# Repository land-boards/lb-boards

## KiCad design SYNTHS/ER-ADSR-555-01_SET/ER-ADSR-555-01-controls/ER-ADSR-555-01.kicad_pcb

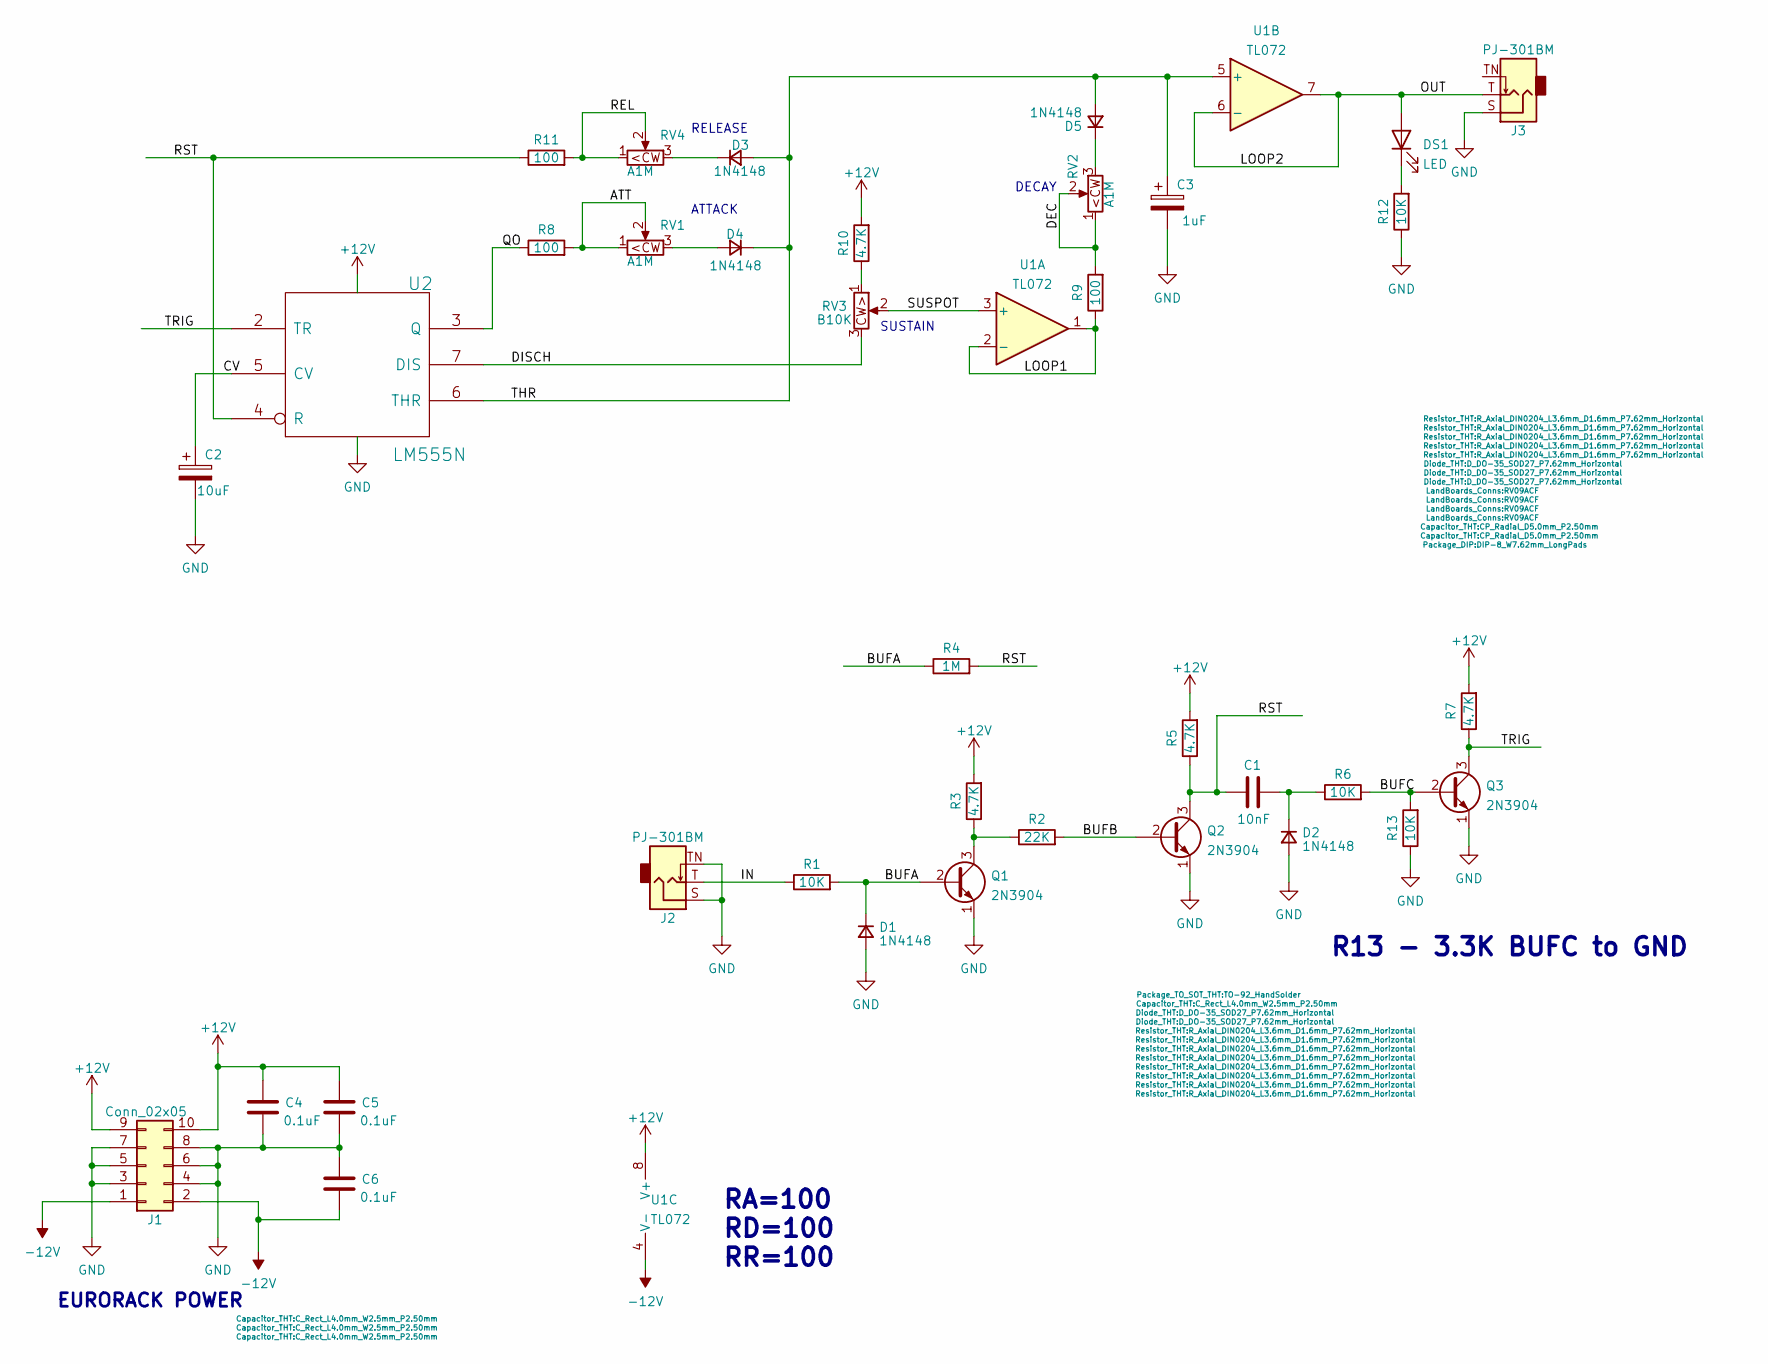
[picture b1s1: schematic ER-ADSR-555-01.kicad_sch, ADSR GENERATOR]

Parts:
C1: 10nF; C_Rect_L4.0mm_W2.5mm_P2.50mm
C2: 10uF; CP_Radial_D5.0mm_P2.50mm
C3: 1uF; CP_Radial_D5.0mm_P2.50mm
C4, C5, C6: 0.1uF; C_Rect_L4.0mm_W2.5mm_P2.50mm
D1, D2, D3, D4, D5: 1N4148; D_DO-35_SOD27_P7.62mm_Horizontal
DS1: LED; LED_D5.0mm
J1: Conn_02x05; IDC-Header_2x05_P2.54mm_Vertical
J2, J3: PJ-301BM; Jack_3.5mm_QingPu_WQP-PJ301BM_Vertical
Q1, Q2, Q3: 2N3904; TO-92_HandSolder
R1, R6, R12, R13: 10K; R_Axial_DIN0204_L3.6mm_D1.6mm_P7.62mm_Horizontal
R2: 22K; R_Axial_DIN0204_L3.6mm_D1.6mm_P7.62mm_Horizontal
R3, R5, R7, R10: 4.7K; R_Axial_DIN0204_L3.6mm_D1.6mm_P7.62mm_Horizontal
R4: 1M; R_Axial_DIN0204_L3.6mm_D1.6mm_P7.62mm_Horizontal
R8, R9, R11: 100; R_Axial_DIN0204_L3.6mm_D1.6mm_P7.62mm_Horizontal
RV1, RV2, RV4: A1M; RV09ACF
RV3: B10K; RV09ACF
U1: TL072; DIP-8_W7.62mm
U2: LM555N; DIP-8_W7.62mm_LongPads

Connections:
+12V: C4.2, C5.2, J1.9, J1.10, R3.2, R5.2, R7.2, R10.2, U1.8 (V+), U2.8 (VCC)
-12V: C6.1, J1.1, J1.2, U1.4 (V-)
/ATT: R8.2, RV1.1, RV1.2
/BUFA: D1.1 (K), Q1.2 (B), R1.2, R4.1
/BUFB: Q2.2 (B), R2.2
/BUFC: Q3.2 (B), R6.2, R13.2
/CV: C2.1, U2.5 (CV)
/DEC: R9.2, RV2.1, RV2.2
/DISCH: RV3.3, U2.7 (DIS)
/IN: J2.T, R1.1
/LOOP1: R9.1, U1.1, U1.2 (-)
/LOOP2: DS1.2 (A), J3.T, U1.6 (-), U1.7
/QO: R8.1, U2.3 (Q)
/REL: R11.2, RV4.1, RV4.2
/RST: C1.1, Q2.3 (C), R4.2, R5.1, R11.1, U2.4 (R)
/SUSPOT: RV3.2, U1.3 (+)
/THR: C3.1, D3.2 (A), D4.1 (K), D5.2 (A), U1.5 (+), U2.6 (THR)
/TRIG: Q3.3 (C), R7.1, U2.2 (TR)
GND: C2.2, C3.2, C4.1, C5.1, C6.2, D1.2 (A), D2.2 (A), J1.3, J1.4, J1.5, J1.6, J1.7, J1.8, J2.S, J2.TN, J3.S, Q1.1 (E), Q2.1 (E), Q3.1 (E), R12.1, R13.1, U2.1 (GND)
unnamed: C1.2, D2.1 (K), R6.1
unnamed: D3.1 (K), RV4.3
unnamed: D4.2 (A), RV1.3
unnamed: D5.1 (K), RV2.3
unnamed: DS1.1 (K), R12.2
unnamed: Q1.3 (C), R2.1, R3.1
unnamed: R10.1, RV3.1

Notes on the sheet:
DECAY
EURORACK POWER
RA=100 RD=100 RR=100
R13 - 3.3K BUFC to GND
ATTACK
RELEASE
SUSTAIN

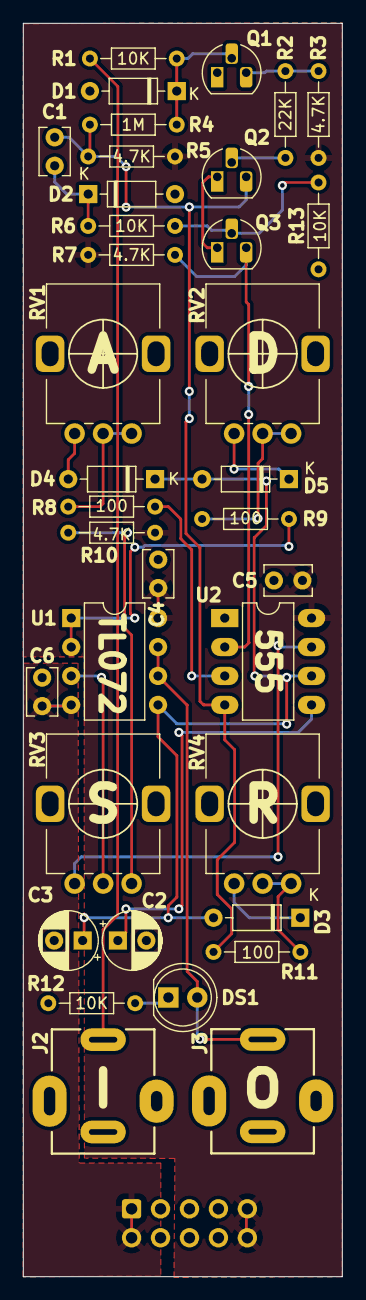
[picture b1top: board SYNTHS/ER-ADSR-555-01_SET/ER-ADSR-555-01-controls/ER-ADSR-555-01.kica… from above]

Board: 2 copper layers, 28.0 x 110.0 mm, 37 parts (1 on the bottom side), 26 nets.

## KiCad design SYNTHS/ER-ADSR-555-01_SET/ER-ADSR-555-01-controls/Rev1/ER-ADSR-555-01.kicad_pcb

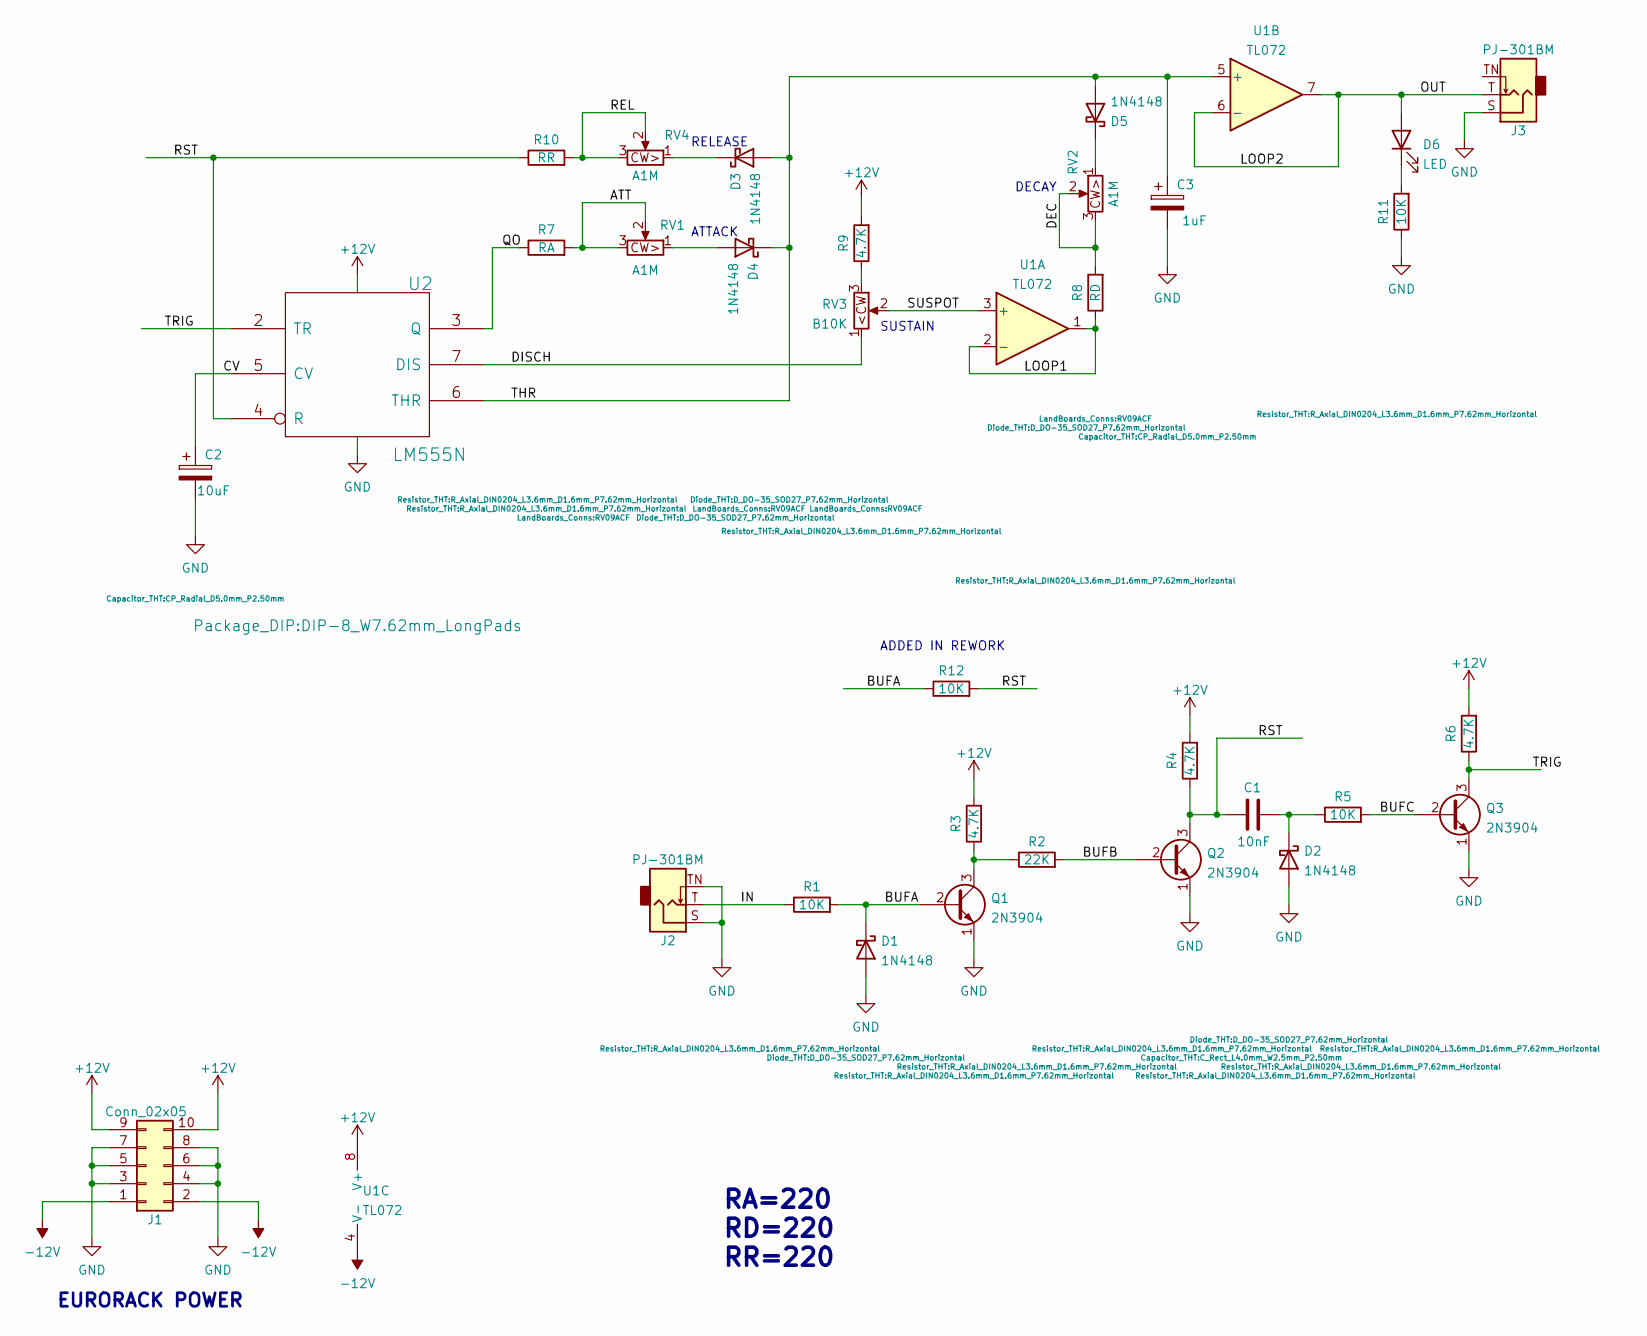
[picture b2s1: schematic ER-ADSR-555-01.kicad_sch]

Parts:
C1: 10nF; C_Rect_L4.0mm_W2.5mm_P2.50mm
C2: 10uF; CP_Radial_D5.0mm_P2.50mm
C3: 1uF; CP_Radial_D5.0mm_P2.50mm
D1, D2, D3, D4, D5: 1N4148; D_DO-35_SOD27_P7.62mm_Horizontal
D6: LED; LED_D5.0mm
J1: Conn_02x05; IDC-Header_2x05_P2.54mm_Vertical
J2, J3: PJ-301BM; Jack_3.5mm_QingPu_WQP-PJ301BM_Vertical
Q1, Q2, Q3: 2N3904; TO-92_Inline
R1, R5, R11, R12: 10K; R_Axial_DIN0204_L3.6mm_D1.6mm_P7.62mm_Horizontal
R2: 22K; R_Axial_DIN0204_L3.6mm_D1.6mm_P7.62mm_Horizontal
R3, R4, R6, R9: 4.7K; R_Axial_DIN0204_L3.6mm_D1.6mm_P7.62mm_Horizontal
R7: RA; R_Axial_DIN0204_L3.6mm_D1.6mm_P7.62mm_Horizontal
R8: RD; R_Axial_DIN0204_L3.6mm_D1.6mm_P7.62mm_Horizontal
R10: RR; R_Axial_DIN0204_L3.6mm_D1.6mm_P7.62mm_Horizontal
RV1, RV2, RV4: A1M; RV09ACF
RV3: B10K; RV09ACF
U1: TL072; DIP-8_W7.62mm
U2: LM555N; DIP-8_W7.62mm_LongPads

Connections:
+12V: J1.9, J1.10, R3.2, R4.2, R6.2, R9.2, U1.8 (V+), U2.8 (VCC)
-12V: J1.1, J1.2, U1.4 (V-)
/ATT: R7.2, RV1.2, RV1.3
/BUFA: D1.1 (K), Q1.2 (B), R1.2, R12.1
/BUFB: Q2.2 (B), R2.2
/BUFC: Q3.2 (B), R5.2
/CV: C2.1, U2.5 (CV)
/DEC: R8.2, RV2.2, RV2.3
/DISCH: RV3.1, U2.7 (DIS)
/IN: J2.T, R1.1
/LOOP1: R8.1, U1.1, U1.2 (-)
/LOOP2: D6.2 (A), J3.T, U1.6 (-), U1.7
/QO: R7.1, U2.3 (Q)
/REL: R10.2, RV4.2, RV4.3
/RST: C1.1, Q2.3 (C), R4.1, R10.1, R12.2, U2.4 (R)
/SUSPOT: RV3.2, U1.3 (+)
/THR: C3.1, D3.2 (A), D4.1 (K), D5.2 (A), U1.5 (+), U2.6 (THR)
/TRIG: Q3.3 (C), R6.1, U2.2 (TR)
GND: C2.2, C3.2, D1.2 (A), D2.2 (A), J1.3, J1.4, J1.5, J1.6, J1.7, J1.8, J2.S, J2.TN, J3.S, Q1.1 (E), Q2.1 (E), Q3.1 (E), R11.1, U2.1 (GND)
unnamed: C1.2, D2.1 (K), R5.1
unnamed: D3.1 (K), RV4.1
unnamed: D4.2 (A), RV1.1
unnamed: D5.1 (K), RV2.1
unnamed: D6.1 (K), R11.2
unnamed: Q1.3 (C), R2.1, R3.1
unnamed: R9.1, RV3.3

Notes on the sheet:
DECAY
EURORACK POWER
RA=220 RD=220 RR=220
ATTACK
RELEASE
SUSTAIN
ADDED IN REWORK

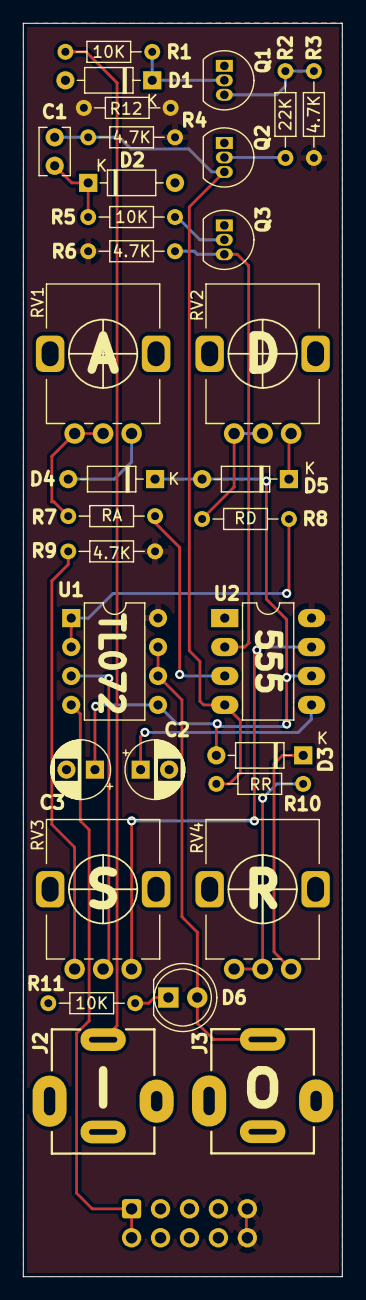
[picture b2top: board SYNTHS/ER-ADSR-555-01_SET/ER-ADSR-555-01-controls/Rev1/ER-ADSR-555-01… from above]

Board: 2 copper layers, 28.0 x 110.0 mm, 33 parts (1 on the bottom side), 26 nets.

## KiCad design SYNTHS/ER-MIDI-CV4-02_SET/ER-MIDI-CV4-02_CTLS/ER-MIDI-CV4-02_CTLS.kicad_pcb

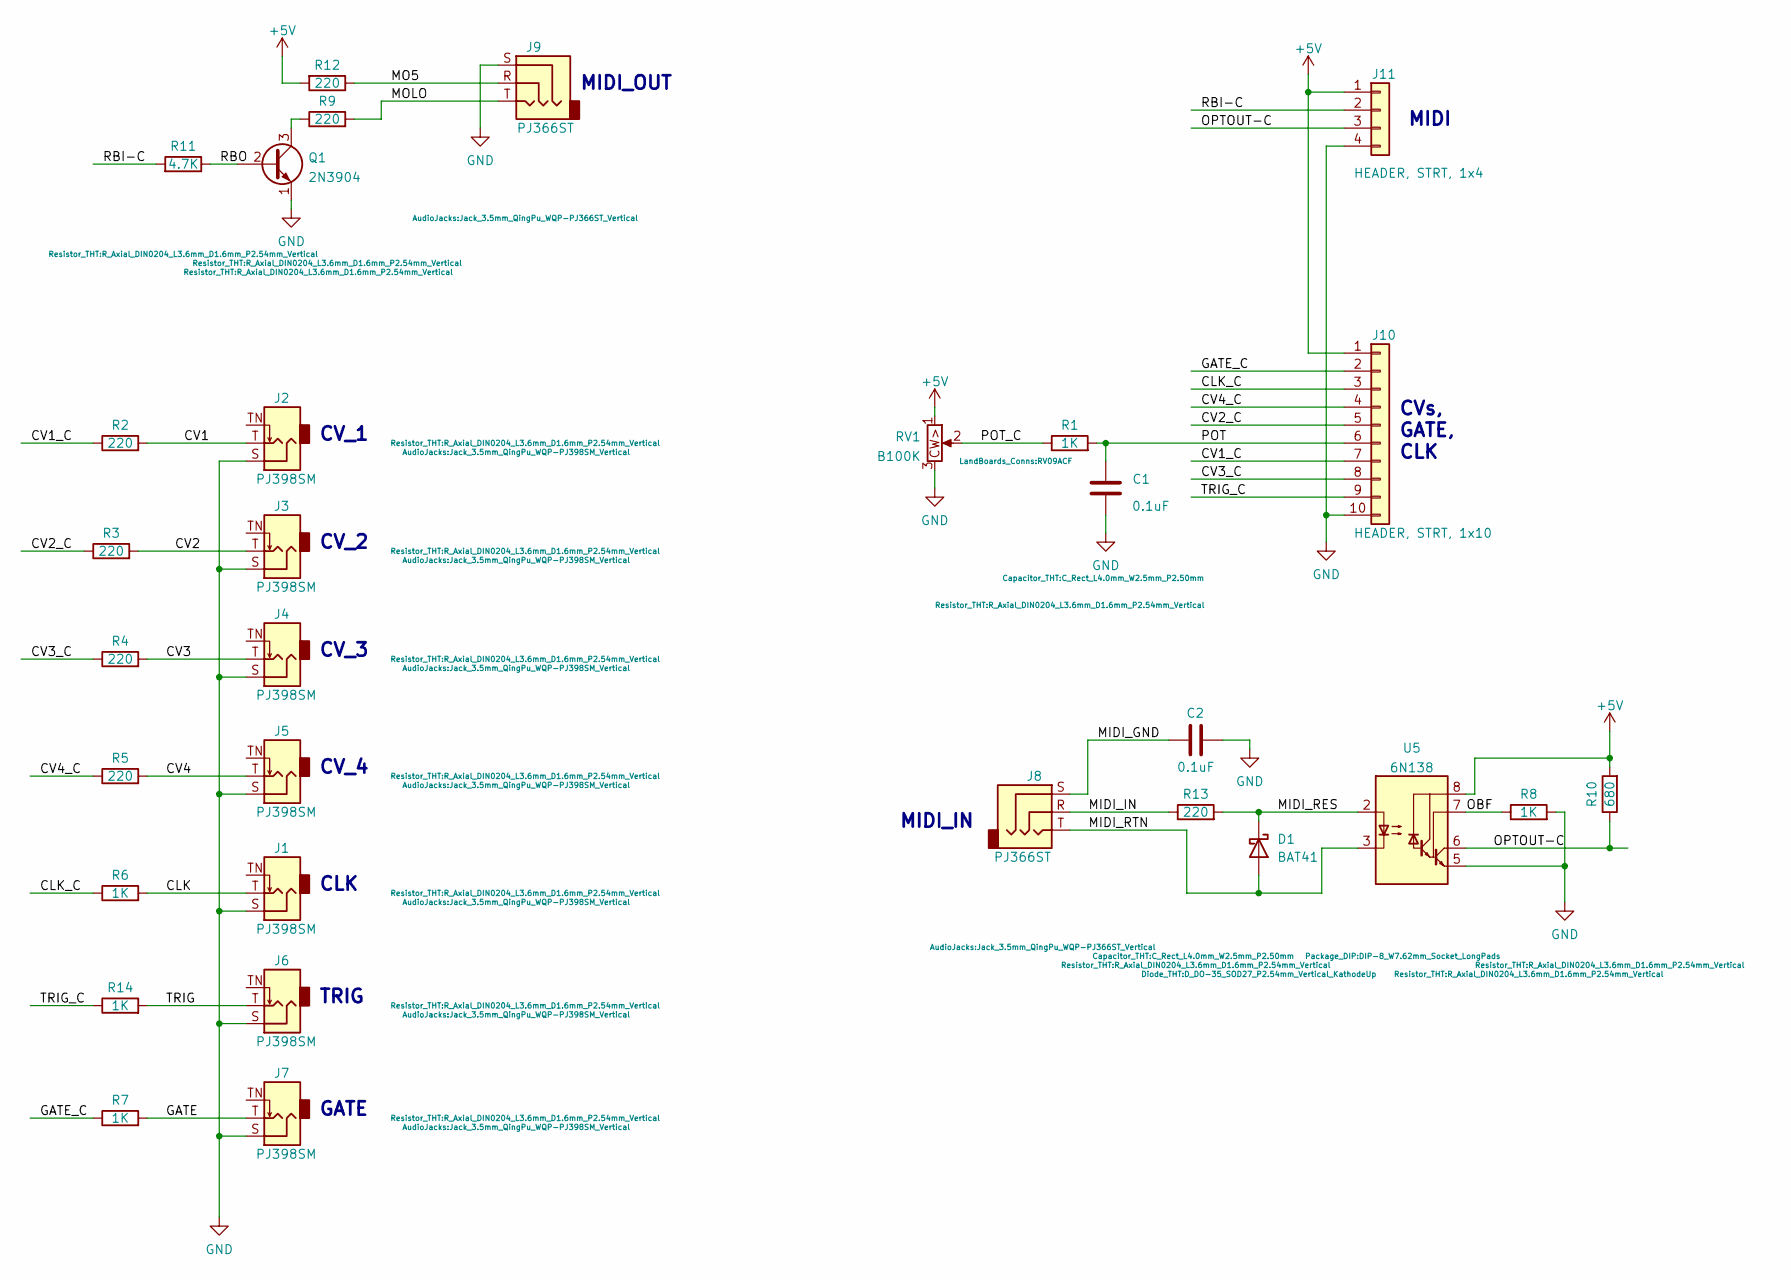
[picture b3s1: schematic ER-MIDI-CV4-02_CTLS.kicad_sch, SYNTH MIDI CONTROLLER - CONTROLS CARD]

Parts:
C1, C2: 0.1uF; C_Rect_L4.0mm_W2.5mm_P2.50mm
D1: BAT41; D_DO-35_SOD27_P2.54mm_Vertical_KathodeUp
J1, J2, J3, J4, J5, J6, J7: PJ398SM; Jack_3.5mm_QingPu_WQP-PJ398SM_Vertical
J8, J9: PJ366ST; Jack_3.5mm_QingPu_WQP-PJ366ST_Vertical
J10: HEADER, STRT, 1x10; PinHeader_1x10_P2.54mm_Vertical
J11: HEADER, STRT, 1x4; PinHeader_1x04_P2.54mm_Vertical
Q1: 2N3904; TO-92_Inline
R1, R6, R7, R8, R14: 1K; R_Axial_DIN0204_L3.6mm_D1.6mm_P2.54mm_Vertical
R2, R3, R4, R5, R9, R12, R13: 220; R_Axial_DIN0204_L3.6mm_D1.6mm_P2.54mm_Vertical
R10: 680; R_Axial_DIN0204_L3.6mm_D1.6mm_P2.54mm_Vertical
R11: 4.7K; R_Axial_DIN0204_L3.6mm_D1.6mm_P2.54mm_Vertical
RV1: B100K; RV09ACF
U5: 6N138; DIP-8_W7.62mm_Socket_LongPads

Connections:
+5V: J10.1, J11.1, R10.2, R12.2, RV1.1, U5.8 (VCC)
/CLK: J1.T, R6.2
/CLK_C: J10.3, R6.1
/CV1: J2.T, R2.2
/CV1_C: J10.7, R2.1
/CV2: J3.T, R3.2
/CV2_C: J10.5, R3.1
/CV3: J4.T, R4.2
/CV3_C: J10.8, R4.1
/CV4: J5.T, R5.2
/CV4_C: J10.4, R5.1
/GATE: J7.T, R7.2
/GATE_C: J10.2, R7.1
/MIDI_GND: C2.1, J8.S
/MIDI_IN: J8.R, R13.1
/MIDI_RES: D1.1 (K), R13.2, U5.2 (C1)
/MIDI_RTN: D1.2 (A), J8.T, U5.3 (C2)
/MO5: J9.R, R12.1
/MOLO: J9.T, R9.2
/OBF: R8.1, U5.7 (VO1)
/OPTOUT-C: J11.3, R10.1, U5.6 (VO2)
/POT: C1.2, J10.6, R1.2
/POT_C: R1.1, RV1.2
/RBI-C: J11.2, R11.2
/RBO: Q1.2 (B), R11.1
/TRIG: J6.T, R14.2
/TRIG_C: J10.9, R14.1
GND: C1.1, C2.2, J1.S, J2.S, J3.S, J4.S, J5.S, J6.S, J7.S, J9.S, J10.10, J11.4, Q1.1 (E), R8.2, RV1.3, U5.5 (GND)
unnamed: Q1.3 (C), R9.1

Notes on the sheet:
CV_1
CV_3
GATE
MIDI_IN
MIDI_OUT
CLK
MIDI
CVs, GATE, CLK
TRIG
CV_4
CV_2

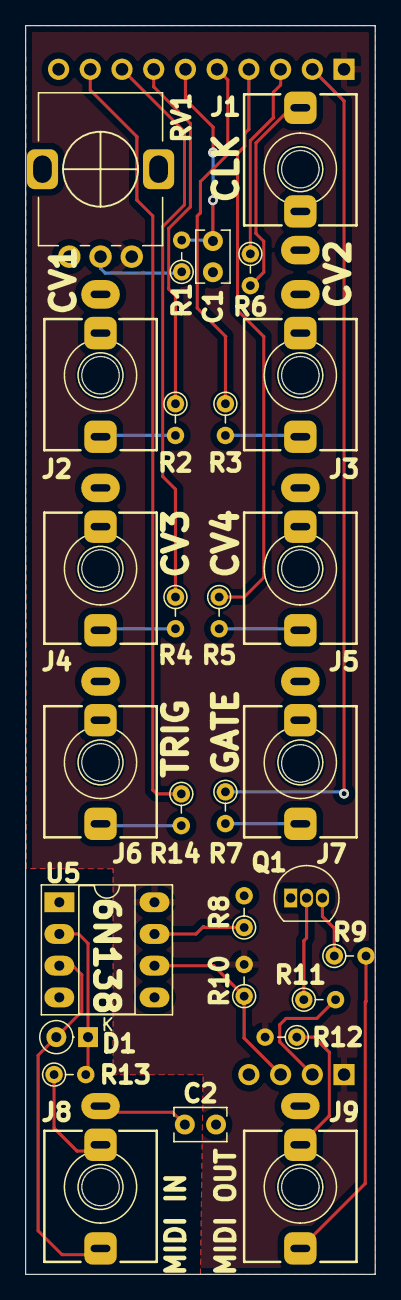
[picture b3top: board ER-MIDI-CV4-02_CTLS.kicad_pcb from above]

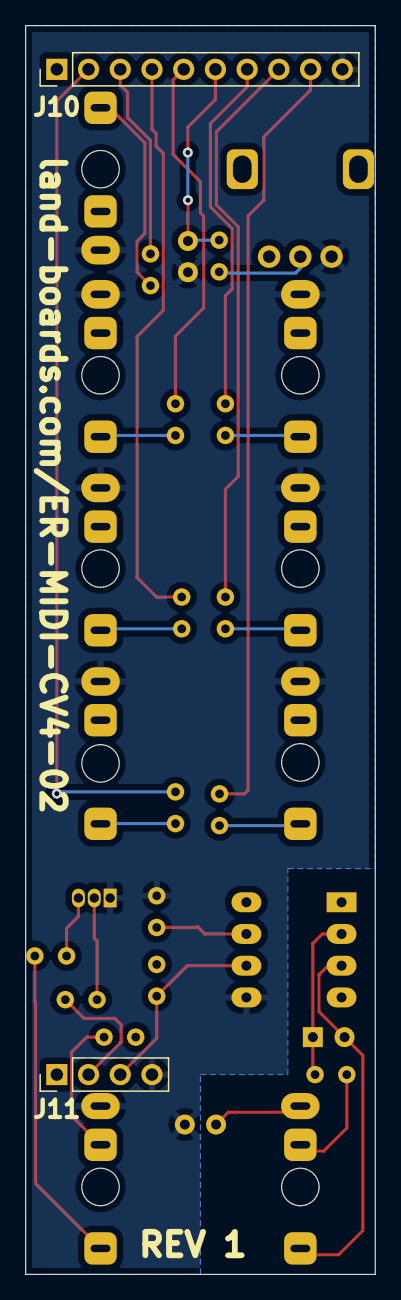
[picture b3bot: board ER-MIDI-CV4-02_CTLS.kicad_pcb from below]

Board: 2 copper layers, 28.0 x 100.0 mm, 31 parts (2 on the bottom side), 29 nets.

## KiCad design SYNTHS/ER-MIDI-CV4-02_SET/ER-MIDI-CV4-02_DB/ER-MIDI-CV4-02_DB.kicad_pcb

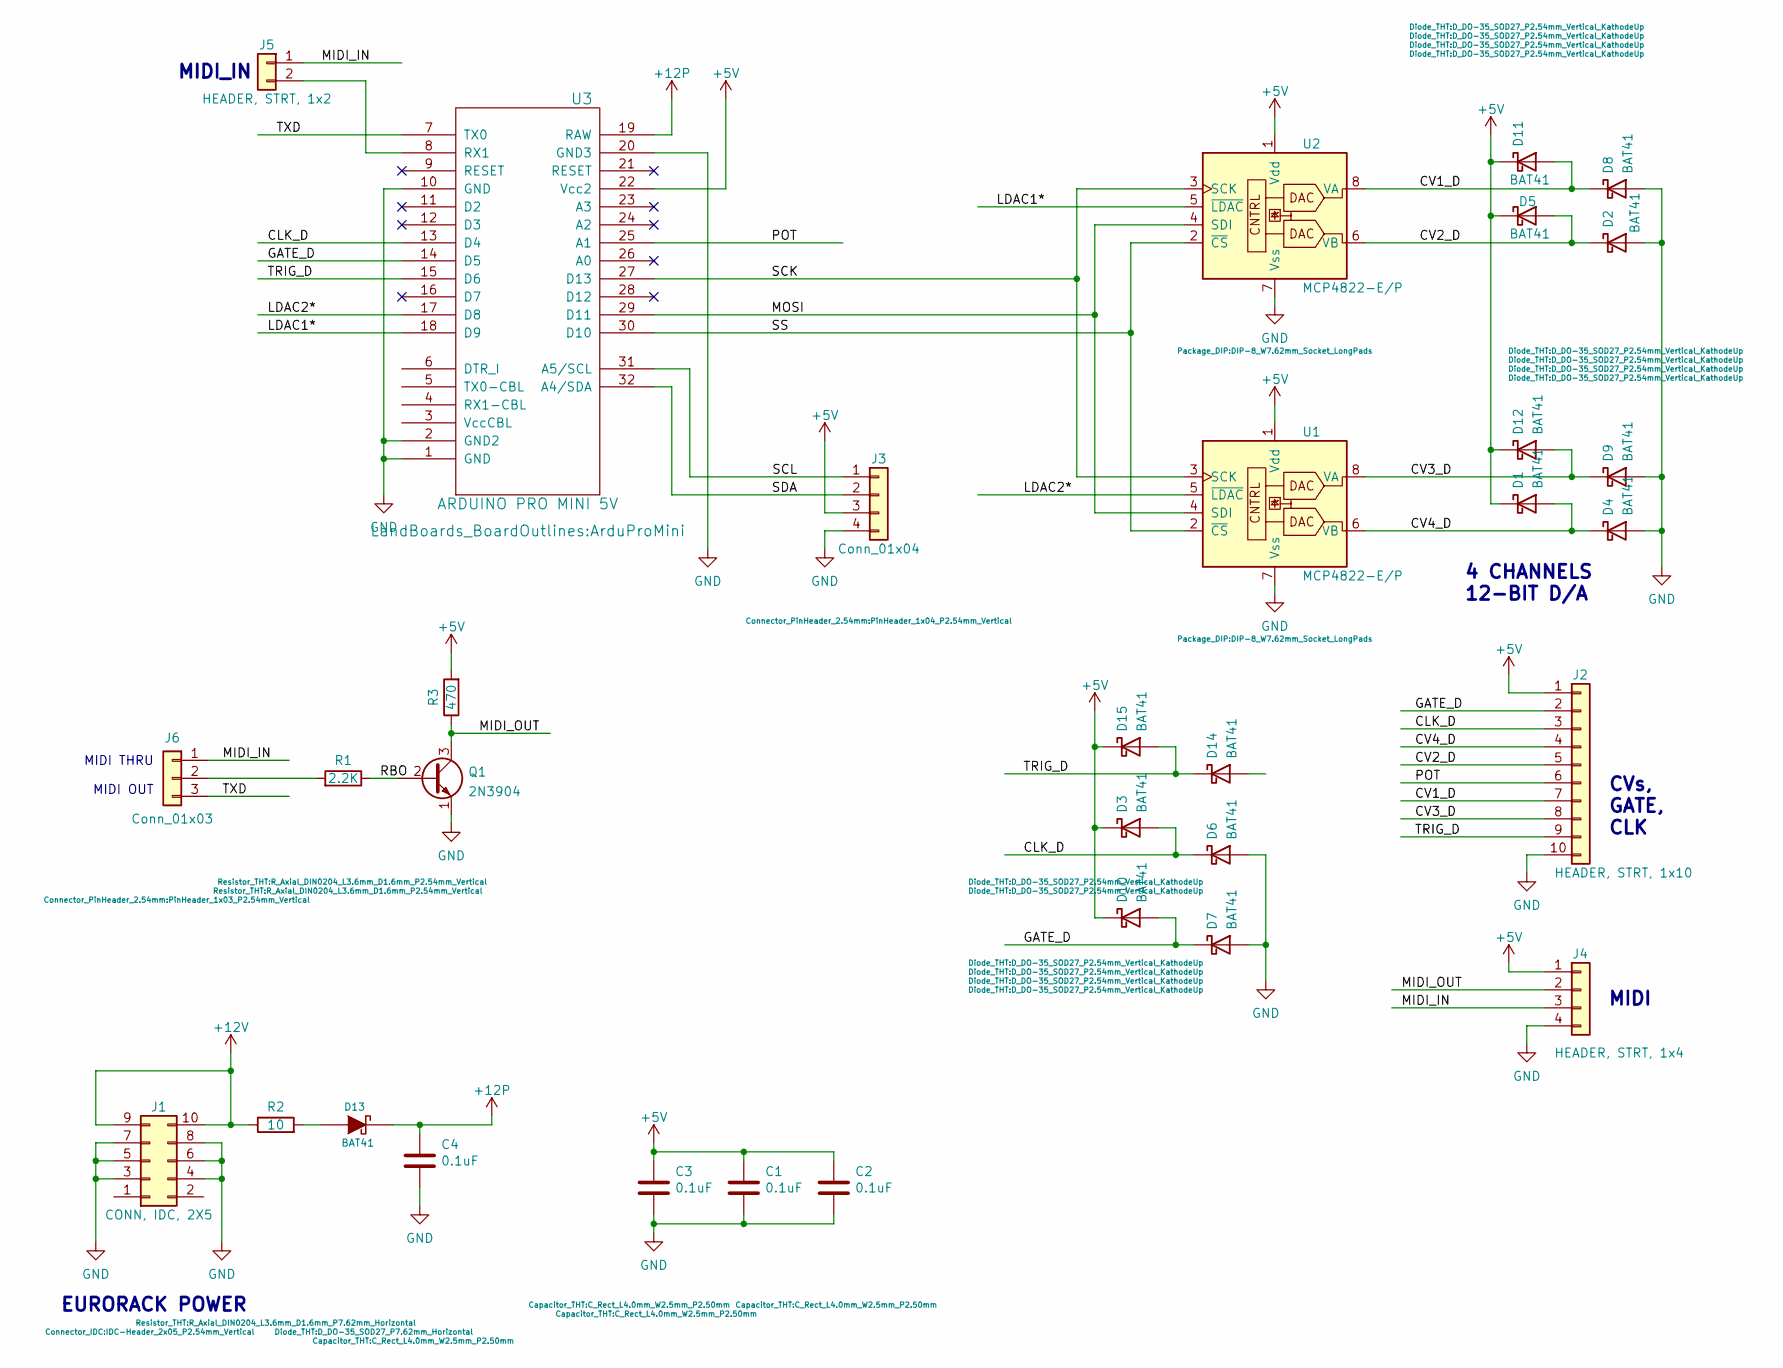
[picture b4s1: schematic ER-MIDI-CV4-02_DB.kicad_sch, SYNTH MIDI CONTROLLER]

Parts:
C1, C2, C3, C4: 0.1uF; C_Rect_L4.0mm_W2.5mm_P2.50mm
D1, D2, D3, D4, D5, D6, D7, D8, D9, D10, D11, D12, D14, D15: BAT41; D_DO-35_SOD27_P2.54mm_Vertical_KathodeUp
D13: BAT41; D_DO-35_SOD27_P7.62mm_Horizontal
J1: CONN, IDC, 2X5; IDC-Header_2x05_P2.54mm_Vertical
J2: HEADER, STRT, 1x10; PinHeader_1x10_P2.54mm_Vertical
J3: Conn_01x04; PinHeader_1x04_P2.54mm_Vertical
J4: HEADER, STRT, 1x4; PinHeader_1x04_P2.54mm_Vertical
J5: HEADER, STRT, 1x2; PinHeader_1x02_P2.54mm_Vertical
J6: Conn_01x03; PinHeader_1x03_P2.54mm_Vertical
Q1: 2N3904; TO-92_Inline
R1: 2.2K; R_Axial_DIN0204_L3.6mm_D1.6mm_P2.54mm_Vertical
R2: 10; R_Axial_DIN0204_L3.6mm_D1.6mm_P7.62mm_Horizontal
R3: 470; R_Axial_DIN0204_L3.6mm_D1.6mm_P2.54mm_Vertical
U1, U2: MCP4822-E/P; DIP-8_W7.62mm_Socket_LongPads
U3: ARDUINO PRO MINI 5V; ArduProMini

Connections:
+5V: C1.1, C2.1, C3.1, D1.1 (K), D3.1 (K), D5.1 (K), D10.1 (K), D11.1 (K), D12.1 (K), D15.1 (K), J2.1, J3.3, J4.1, R3.2, U1.1 (Vdd), U2.1 (Vdd), U3.22 (Vcc2)
+12P: C4.1, D13.1 (K), U3.19 (RAW)
+12V: J1.9, J1.10, R2.1
/CLK_D: D3.2 (A), D6.1 (K), J2.3, U3.13 (D4)
/CV1_D: D8.1 (K), D11.2 (A), J2.7, U2.8 (VA)
/CV2_D: D2.1 (K), D5.2 (A), J2.5, U2.6 (VB)
/CV3_D: D9.1 (K), D12.2 (A), J2.8, U1.8 (VA)
/CV4_D: D1.2 (A), D4.1 (K), J2.4, U1.6 (VB)
/GATE_D: D7.1 (K), D10.2 (A), J2.2, U3.14 (D5)
/LDAC1*: U2.5 (~LDAC), U3.18 (D9)
/LDAC2*: U1.5 (~LDAC), U3.17 (D8)
/MIDI_IN: J4.3, J5.1, J6.1
/MIDI_OUT: J4.2, Q1.3 (C), R3.1
/MOSI: U1.4 (SDI), U2.4 (SDI), U3.29 (D11)
/POT: J2.6, U3.25 (A1)
/RBO: Q1.2 (B), R1.1
/SCK: U1.3 (SCK), U2.3 (SCK), U3.27 (D13)
/SCL: J3.1, U3.31 (A5/SCL)
/SDA: J3.2, U3.32 (A4/SDA)
/SS: U1.2 (~CS), U2.2 (~CS), U3.30 (D10)
/TRIG_D: D14.1 (K), D15.2 (A), J2.9, U3.15 (D6)
/TXD: J6.3, U3.7 (TX0)
GND: C1.2, C2.2, C3.2, C4.2, D2.2 (A), D4.2 (A), D6.2 (A), D7.2 (A), D8.2 (A), D9.2 (A), J1.3, J1.4, J1.5, J1.6, J1.7, J1.8, J2.10, J3.4, J4.4, Q1.1 (E), U1.7 (Vss), U2.7 (Vss), U3.1 (GND), U3.2 (GND2), U3.10 (GND), U3.20 (GND3)
unnamed: D13.2 (A), R2.2
unnamed: J5.2, U3.8 (RX1)
unnamed: J6.2, R1.2

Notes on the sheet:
CVs, GATE, CLK
MIDI_IN
4 CHANNELS 12-BIT D/A
MIDI THRU MIDI OUT
MIDI
EURORACK POWER

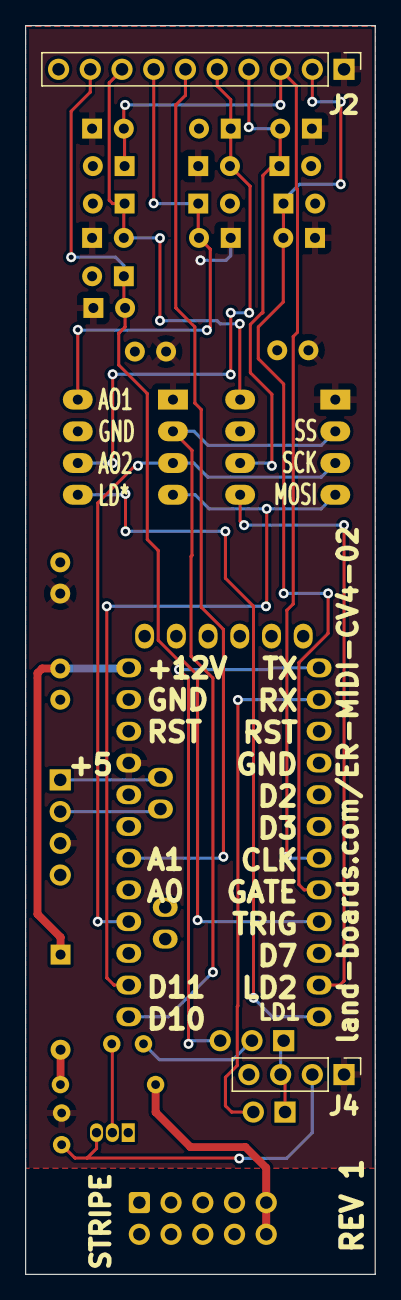
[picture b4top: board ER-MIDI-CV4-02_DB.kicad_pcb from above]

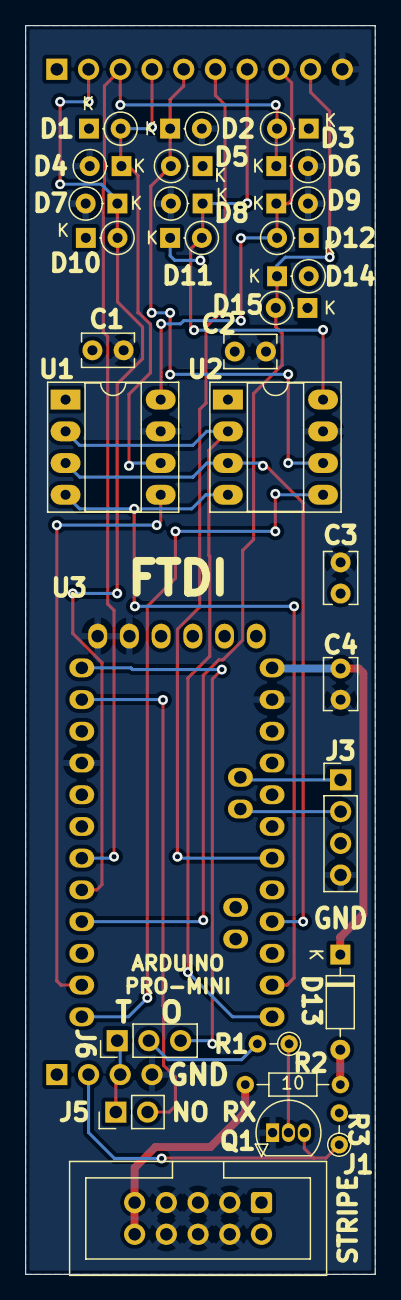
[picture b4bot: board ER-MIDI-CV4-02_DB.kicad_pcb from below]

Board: 2 copper layers, 28.0 x 100.0 mm, 32 parts (30 on the bottom side), 26 nets.
